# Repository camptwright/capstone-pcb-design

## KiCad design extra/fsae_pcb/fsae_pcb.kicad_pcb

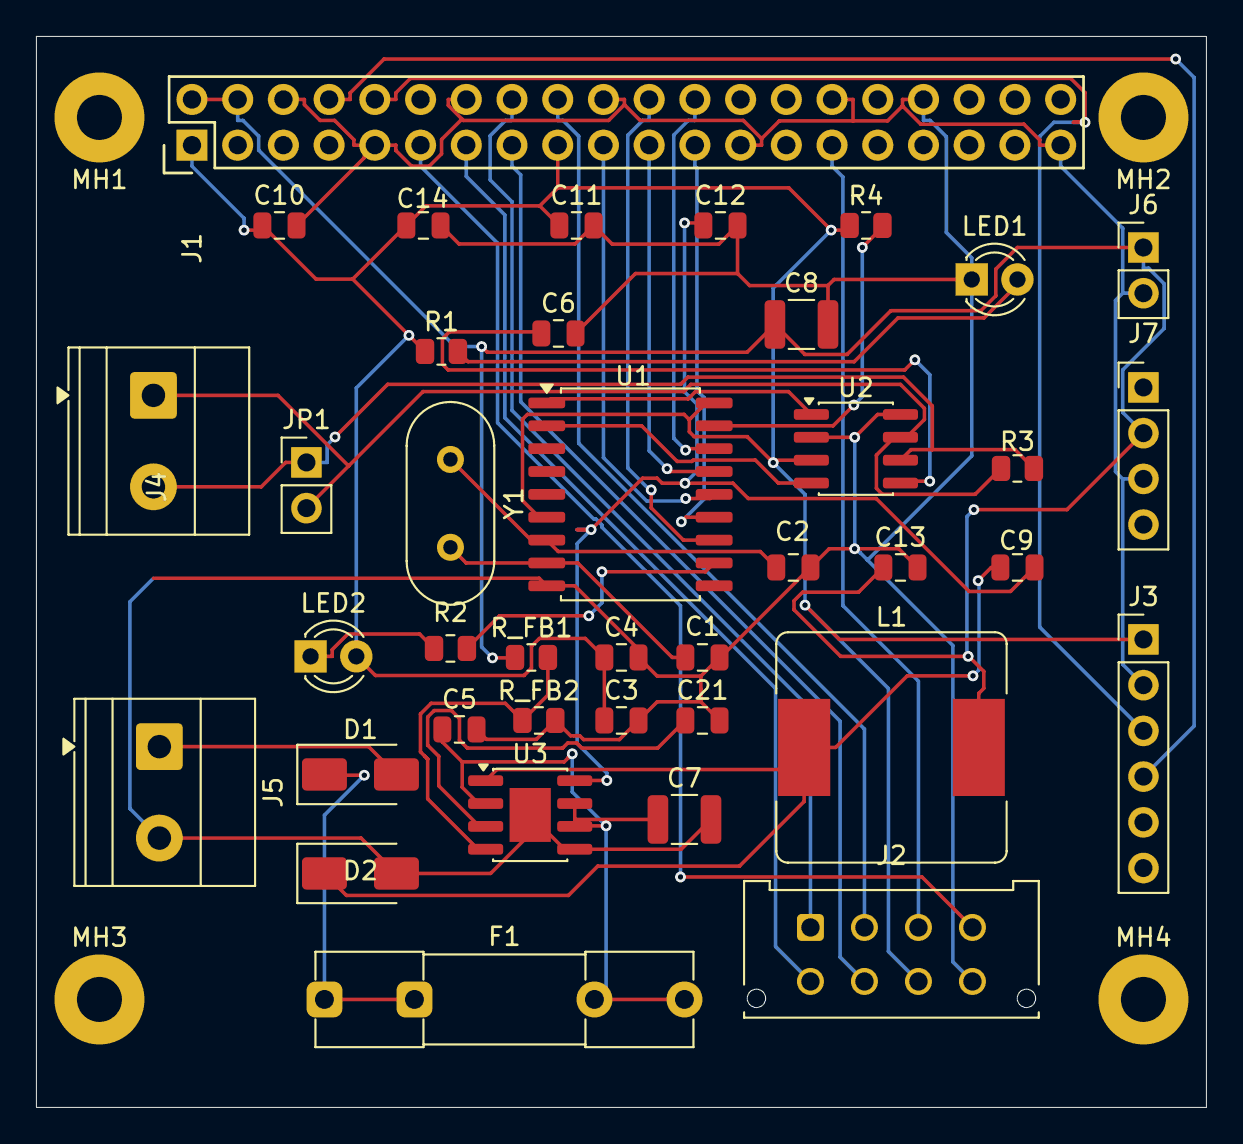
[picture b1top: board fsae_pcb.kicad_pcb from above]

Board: 2 copper layers, 65.0 x 59.5 mm, 43 parts (0 on the bottom side), 34 nets.

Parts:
C1, C5, C6, C9, C21: C; C_0805_2012Metric
C2: 22pF; C_0805_2012Metric
C3, C4, C10, C11, C12: 110nF; C_0805_2012Metric
C7, C8: C; C_1210_3225Metric
C13, C14: 10microF; C_0805_2012Metric
D1, D2: D_Schottky; D_SMA
F1: Fuse; Fuseholder_Clip-5x20mm_Littelfuse_111_Inline_P20.00x5.00mm_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
J1: Conn_02x20_Odd_Even; Pin_Header_Straight_2x20
J2: Conn_02x04_Odd_Even; Molex_Micro-Fit_3.0_43045-0812_2x04_P3.00mm_Vertical
J3: Conn_01x06; PinHeader_1x06_P2.54mm_Vertical
J4, J5: Screw_Terminal_01x02; TerminalBlock_Phoenix_MKDS-1,5-2-5.08_1x02_P5.08mm_Horizont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
J6: Conn_01x02; PinHeader_1x02_P2.54mm_Vertical
J7: Conn_01x04; PinHeader_1x04_P2.54mm_Vertical
JP1: Conn_01x02; PinHeader_1x02_P2.54mm_Vertical
L1: L; L_Bourns_SRR1260
LED1, LED2: LED; LED_D3.0mm
MH1, MH2, MH3, MH4: MountingHole_2.5mm_Pad
R1, R2: 330; R_0805_2012Metric
R3: 120; R_0805_2012Metric
R4: 10k; R_0805_2012Metric
R_FB1, R_FB2: R; R_0805_2012Metric
U1: MCP2515-xSO; SOIC-18W_7.5x11.6mm_P1.27mm
U2: SN65HVD230; SOIC-8_3.9x4.9mm_P1.27mm
U3: MP1584EN-LF-Z; SOIC-8-1EP_3.9x4.9mm_P1.27mm_EP2.29x3mm
Y1: Crystal; Crystal_HC49-4H_Vertical

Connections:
+3V3: C3.1, C4.1, C10.1, C11.1, C14.1, J1.1, J1.17, J2.7, J3.1, LED2.2 (A), R1.1, R4.1, U1.6 (~TX2RTS), U1.18 (VDD), U2.3 (VCC)
+5V: C8.1, C13.1, J1.2, J1.4, J6.1, J7.2, L1.2, R_FB1.1
+12V: D1.2 (A), J5.1
/BTN1: J1.11, J2.4
/BTN2: J1.13, J2.5
/BTN3: J1.15, J2.6
/GPS_RX: J1.8, J3.4
/GPS_TX: J1.10, J3.3
/LED_DB1: J1.16, J2.1
/LED_DB2: J1.18, J2.2
/LED_DB3: J1.29, J2.3
/MCP_INT: J1.22, U1.12 (~INT)
/SPI_CE0: J1.24, U1.16 (~CS)
/SPI_MISO: J1.21, U1.15 (SO)
/SPI_MOSI: J1.19, U1.14 (SI)
/SPI_SCK: J1.23, U1.13 (SCK)
GND: C1.2, C2.2, C3.2, C4.2, C5.2, C6.2, C7.2, C8.2, C10.2, C11.2, C12.2, C13.2, C14.2, C21.2, D2.2 (A), J1.6, J1.9, J1.14, J1.20, J1.25, J1.30, J1.34, J1.39, J2.8, J3.2, J5.2, J6.2, J7.3, LED1.1 (K), R_FB2.2, U1.9 (VSS), U2.2 (GND), U2.8 (Rs), U3.5 (GND), U3.9 (EPAD)
unnamed: D1.1 (K), F1.1
unnamed: C9.1, D2.1 (K), L1.1, U3.1 (SW)
unnamed: J4.1, JP1.2, R3.1, U2.7 (CANH)
unnamed: J4.2, JP1.1, R3.2, U2.6 (CANL)
unnamed: LED1.2 (A), R1.2
unnamed: LED2.1 (K), R2.1
unnamed: C1.1, U1.8 (OSC1), Y1.2
unnamed: C2.1, U1.7 (OSC2), Y1.1
unnamed: U1.2 (RXCAN), U2.4 (R)
unnamed: U1.1 (TXCAN), U2.1 (D)
unnamed: R4.2, U1.17 (~RESET)
unnamed: R2.2, U1.11 (~RX0BF)
unnamed: C6.1, U2.5 (Vref)
unnamed: C9.2, C12.1, U3.8 (BST)
unnamed: C21.1, U3.3 (COMP)
unnamed: C5.1, C7.1, F1.2, U3.2 (EN), U3.6 (FREQ), U3.7 (VIN)
unnamed: R_FB1.2, R_FB2.1, U3.4 (FB)

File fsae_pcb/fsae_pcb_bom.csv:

"Id";"Designator";"Footprint";"Quantity";"Designation";"Supplier and ref";
1;"R_FB2,R_FB1";"R_0805_2012Metric";2;"R";;;
2;"JP1,J6";"PinHeader_1x02_P2.54mm_Vertical";2;"Conn_01x02";;;
3;"LED2,LED1";"LED_D3.0mm";2;"LED";;;
4;"F1";"Fuseholder_Clip-5x20mm_Littelfuse_111_Inline_P20.00x5.00mm_D1.05mm_Horizontal";1;"Fuse";;;
5;"J4";"TerminalBlock_Phoenix_MKDS-1,5-3-5.08_1x03_P5.08mm_Horizontal";1;"Screw_Terminal_01x03";;;
6;"C11,C4,C3,C12,C10";"C_0805_2012Metric";5;"110nF";;;
7;"C1,C21,C5,C6,C9";"C_0805_2012Metric";5;"C";;;
8;"R2,R1";"R_0805_2012Metric";2;"330";;;
9;"U3";"SOIC-8-1EP_3.9x4.9mm_P1.27mm_EP2.29x3mm";1;"MP1584EN-LF-Z";;;
10;"C2";"C_0805_2012Metric";1;"22pF";;;
11;"Y1";"Crystal_HC49-4H_Vertical";1;"Crystal";;;
12;"U1";"SOIC-18W_7.5x11.6mm_P1.27mm";1;"MCP2515-xSO";;;
13;"U2";"SOIC-8_3.9x4.9mm_P1.27mm";1;"SN65HVD230";;;
14;"D2,D1";"D_SMA";2;"D_Schottky";;;
15;"C14,C13";"C_0805_2012Metric";2;"10microF";;;
16;"J5";"TerminalBlock_Phoenix_MKDS-1,5-2-5.08_1x02_P5.08mm_Horizontal";1;"Screw_Terminal_01x02";;;
17;"J7";"PinHeader_1x04_P2.54mm_Vertical";1;"Conn_01x04";;;
18;"L1";"L_Bourns_SRR1260";1;"L";;;
19;"C8,C7";"C_1210_3225Metric";2;"C";;;
20;"J1";"Pin_Header_Straight_2x20";1;"Conn_02x20_Odd_Even";;;
21;"R3";"R_0805_2012Metric";1;"120";;;
22;"R4";"R_0805_2012Metric";1;"10k";;;
23;"J2";"Molex_Micro-Fit_3.0_43045-0812_2x04_P3.00mm_Vertical";1;"Conn_02x04_Odd_Even";;;
24;"J3";"PinHeader_1x06_P2.54mm_Vertical";1;"Conn_01x06";;;

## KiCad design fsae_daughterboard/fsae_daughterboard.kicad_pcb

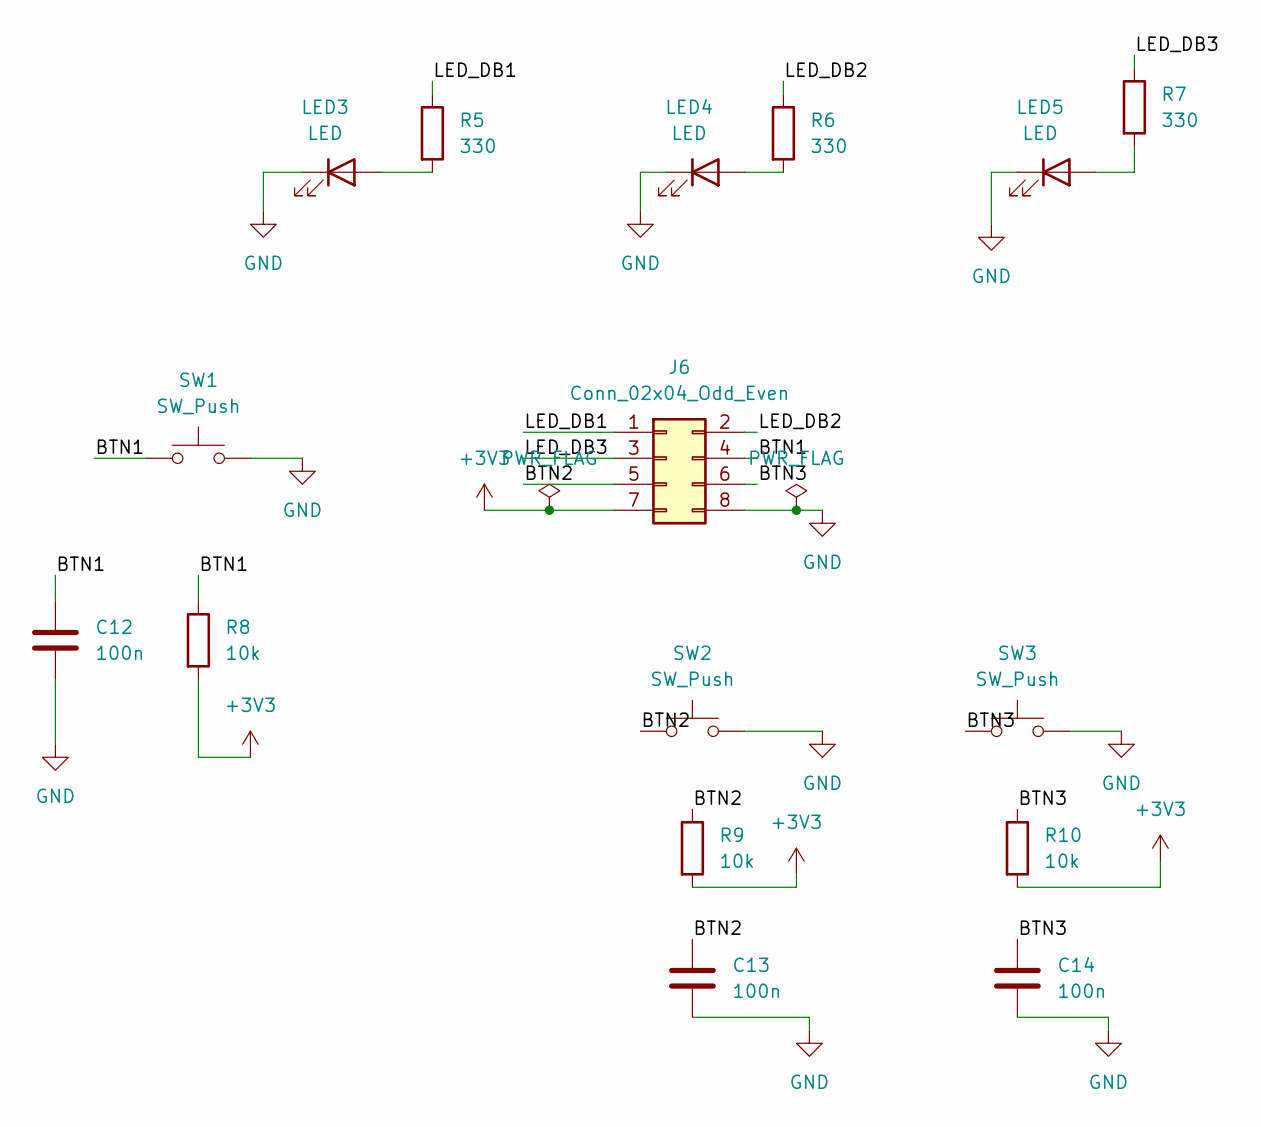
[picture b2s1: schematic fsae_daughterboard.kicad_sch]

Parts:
C12, C13, C14: 100n; C_0805_2012Metric
J6: Conn_02x04_Odd_Even; Molex_Micro-Fit_3.0_43045-0812_2x04_P3.00mm_Vertical
LED3, LED4, LED5: LED; LED_D5.0mm
R5, R6, R7: 330; R_0805_2012Metric
R8, R9, R10: 10k; R_0805_2012Metric
SW1, SW2, SW3: SW_Push; SW_PUSH_6mm_H5mm

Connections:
+3V3: J6.7, R8.2, R9.2, R10.2
/BTN1: C12.1, J6.4, R8.1, SW1.1
/BTN2: C13.1, J6.5, R9.1, SW2.1
/BTN3: C14.1, J6.6, R10.1, SW3.1
/LED_DB1: J6.1, R5.1
/LED_DB2: J6.2, R6.1
/LED_DB3: J6.3, R7.1
GND: C12.2, C13.2, C14.2, J6.8, LED3.1 (K), LED4.1 (K), LED5.1 (K), SW1.2, SW2.2, SW3.2
unnamed: LED3.2 (A), R5.2
unnamed: LED4.2 (A), R6.2
unnamed: LED5.2 (A), R7.2

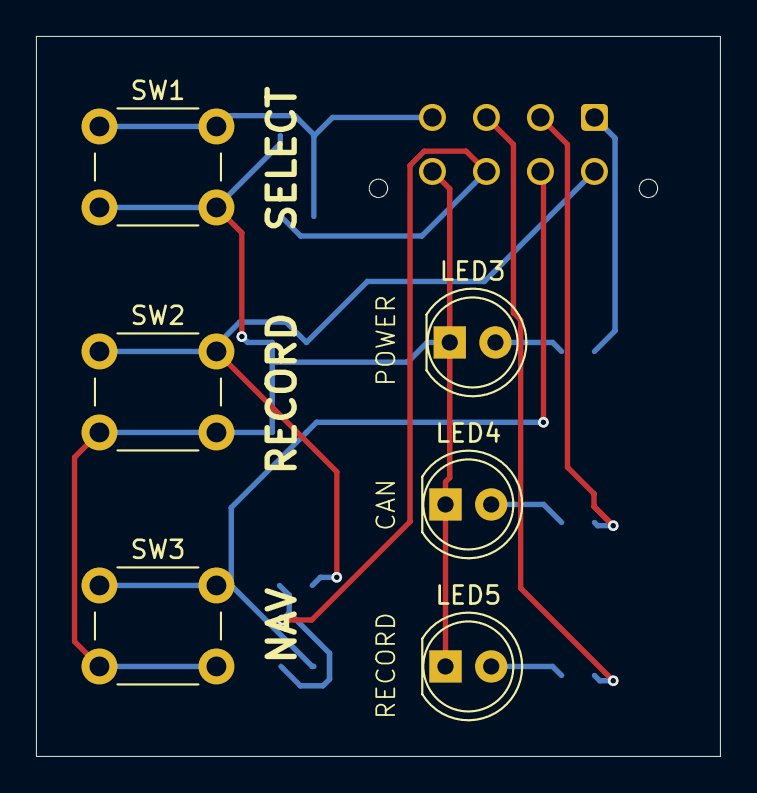
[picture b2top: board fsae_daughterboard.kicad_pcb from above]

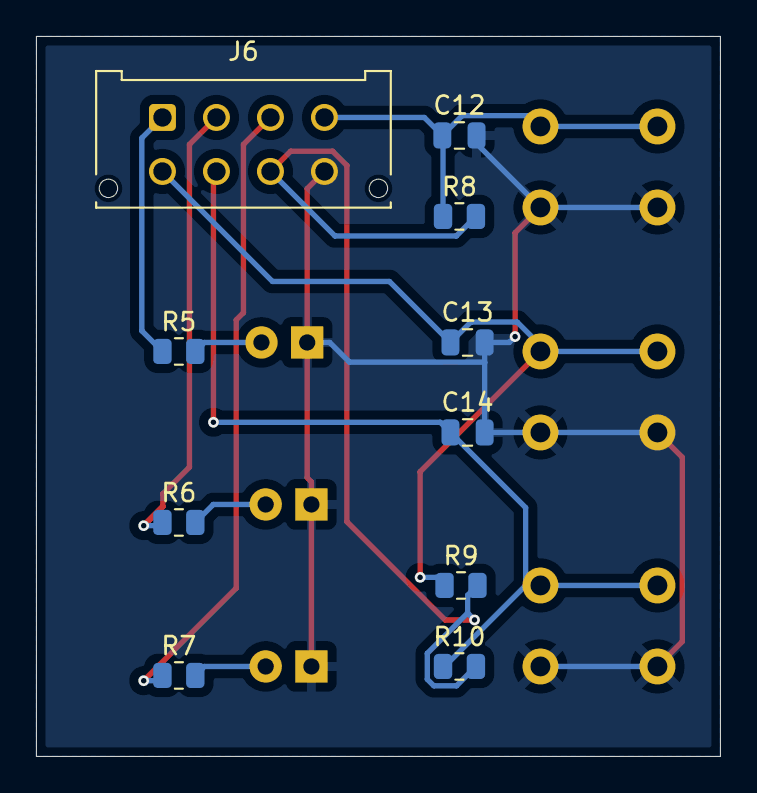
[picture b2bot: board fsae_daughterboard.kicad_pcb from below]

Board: 2 copper layers, 38.0 x 40.0 mm, 16 parts (10 on the bottom side), 11 nets.

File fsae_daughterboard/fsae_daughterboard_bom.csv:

"Id";"Designator";"Footprint";"Quantity";"Designation";"Supplier and ref";
1;"SW2,SW1,SW3";"SW_PUSH_6mm_H5mm";3;"SW_Push";;;
2;"LED3,LED4,LED5";"LED_D5.0mm";3;"LED";;;
3;"R6,R7,R5";"R_0805_2012Metric";3;"330";;;
4;"C13,C14,C12";"C_0805_2012Metric";3;"100n";;;
5;"R8,R10,R9";"R_0805_2012Metric";3;"10k";;;
6;"J6";"Molex_Micro-Fit_3.0_43045-0812_2x04_P3.00mm_Vertical";1;"Conn_02x04_Odd_Even";;;

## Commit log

2026-03-05 new main pcb design
2026-03-10 finished product
2026-03-13 final pcb desgin
